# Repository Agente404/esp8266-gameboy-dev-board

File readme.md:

# ESP8266 Gameboy Dev Board

Your go to dev board for Gameboy accessories development. Put it on top of Wemos D1 mini and have fun.

## Pinout

This board uses the following pins:

D0, D1, D2, D3 (Pull GPIO0 to ground), D4, D8

Hence **IT IS** compatible with Wemos SD card shield. I've remapped conflicting pins as following:

* D5 -> D4
* D6 -> D0
* D7 -> D8

## Part List

The part list is included as a Digikey shopping cart. Quantities are for one (1) board.

Note that EXT PORT AGB connector **is not included**. It must be sourced elsewhere.

## License

See the [blog post here](https://poyu.xyz/projects/esp8266-gameboy-dev-board/) of the original author!

MIT: https://poyu.mit-license.org/

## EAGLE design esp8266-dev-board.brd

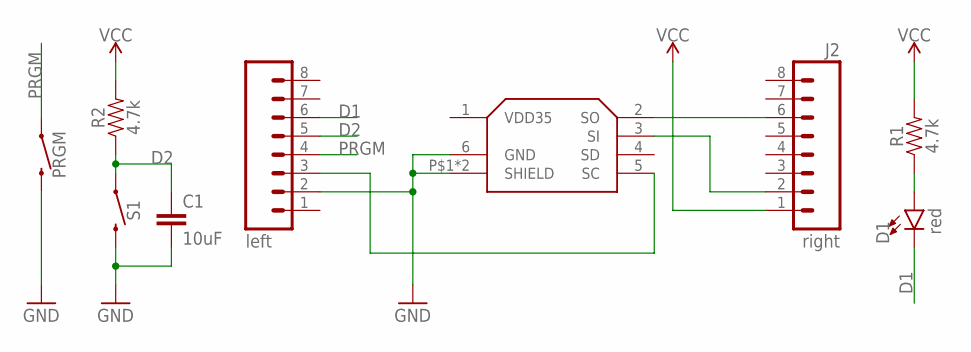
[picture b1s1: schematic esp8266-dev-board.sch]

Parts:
C1: 10uF; 0805
D1: red; LED-0603
J1: left; 1X08_ROUND
J2: right; 1X08_ROUND
PRGM: MOMENTARY-SWITCH-SPST-SMD-6.0X3.5MM; TACTILE_SWITCH_SMD_6.0X3.5MM
R1, R2: 4.7k; 0805
S1: MOMENTARY-SWITCH-SPST-SMD-6.0X3.5MM; TACTILE_SWITCH_SMD_6.0X3.5MM
U$1: EXT-PORT-AGB

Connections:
D1: D1.C, J1.6
D2: C1.1, J1.5, R2.1, S1.1
GND: C1.2, J1.2, PRGM.2, S1.2, U$1.6 (GND), U$1.P$1 (SHIELD), U$1.P$2 (SHIELD)
unnamed: J1.3, U$1.5 (SC)
unnamed: J2.6, U$1.2 (SO)
unnamed: J2.2, U$1.3 (SI)
unnamed: D1.A, R1.1
PRGM: J1.4, PRGM.1
VCC: J2.1, R1.2, R2.2

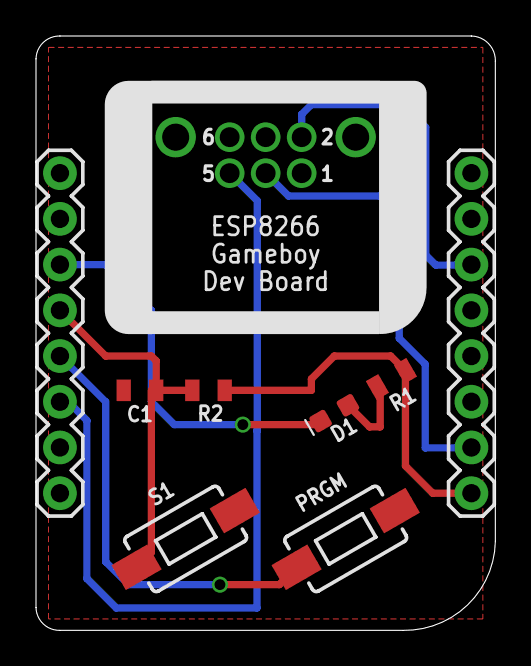
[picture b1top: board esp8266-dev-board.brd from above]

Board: 2 copper layers, 25.5 x 33.0 mm, 9 parts (1 on the bottom side), 9 nets.

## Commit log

2018-10-30 Fix dimensions
2018-10-30 Fix sch warnings
2018-10-30 Fixed zero width polygons and top silkscreen
2018-10-31 Back silkscreen
2018-10-31 MicroSD shield compatibility

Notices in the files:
parts and their libraries:
SparkFun-Capacitors: Licensing: Creative Commons ShareAlike 4.0 International - https://creativecommons.org/licenses/by-sa/4.0
